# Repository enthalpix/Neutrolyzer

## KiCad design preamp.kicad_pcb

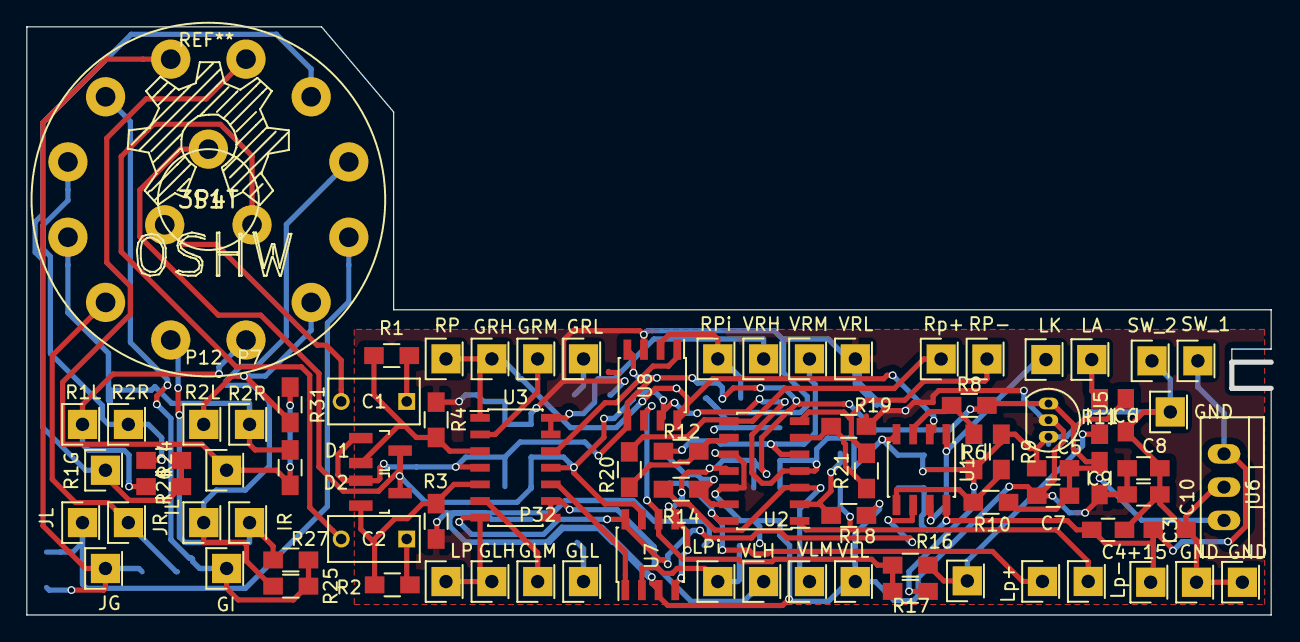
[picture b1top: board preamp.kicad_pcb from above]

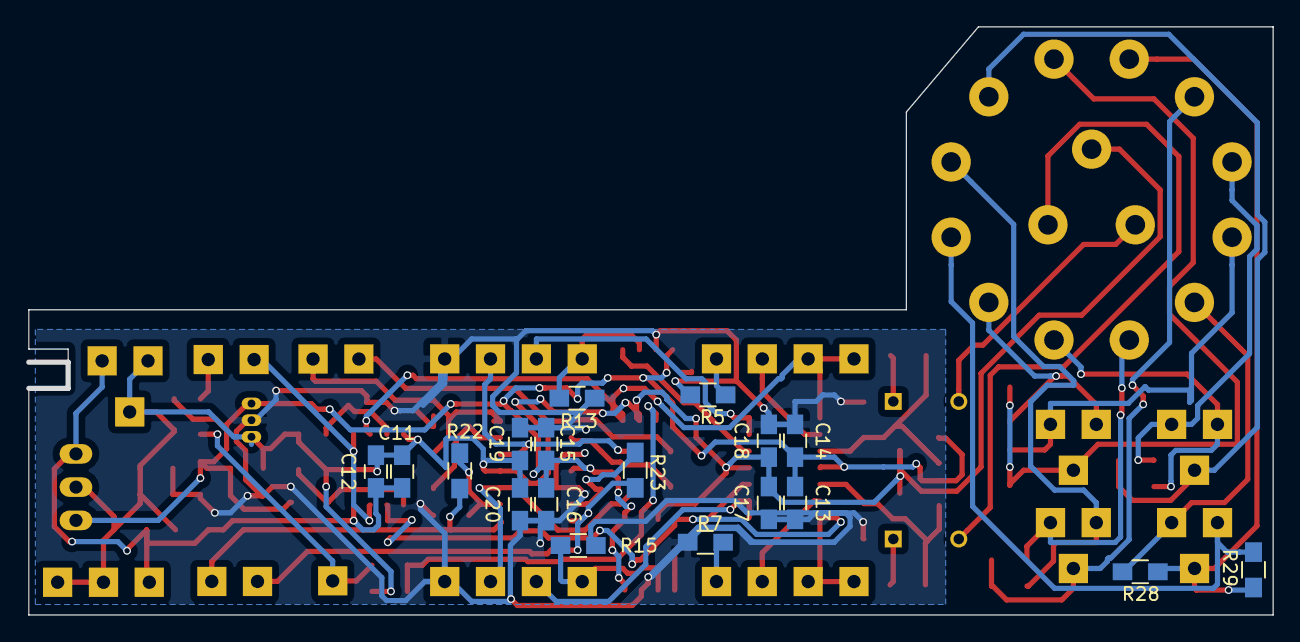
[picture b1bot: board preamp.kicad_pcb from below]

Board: 2 copper layers, 95.0 x 44.9 mm, 102 parts (18 on the bottom side), 50 nets.

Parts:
C1, C2: 470n; C_Rect_L7_W3.5_P5
C3, C5, C7, C8: 1µ; C_0805_HandSoldering
C4, C6, C9, C10, C12, C14, C16, C18, C20: 10n; C_0805_HandSoldering
C11, C13, C15, C17, C19: 100n; C_0805_HandSoldering
D1, D2: D_Schottky_x2_Serial; SOT-23_Handsoldering
P1: R1G; Socket_Strip_Straight_1x01
P2: IR; Socket_Strip_Straight_1x01
P3: GI; Socket_Strip_Straight_1x01
P4, P7: R2R; Socket_Strip_Straight_1x01
P5: IL; Socket_Strip_Straight_1x01
P6: R2G; Socket_Strip_Straight_1x01
P8: R1L; Socket_Strip_Straight_1x01
P9: JG; Socket_Strip_Straight_1x01
P10: JL; Socket_Strip_Straight_1x01
P11: JR; Socket_Strip_Straight_1x01
P12: R2L; Socket_Strip_Straight_1x01
P13, P14, P17: GND; Socket_Strip_Straight_1x01
P16: +15; Socket_Strip_Straight_1x01
P18: Lp-; Socket_Strip_Straight_1x01
P19: Rp+; Socket_Strip_Straight_1x01
P20: LP; Socket_Strip_Straight_1x01
P21: RP; Socket_Strip_Straight_1x01
P22: LPi; Socket_Strip_Straight_1x01
P23: RPi; Socket_Strip_Straight_1x01
P27: RP-; Socket_Strip_Straight_1x01
P28: Lp+; Socket_Strip_Straight_1x01
P29: GRM; Socket_Strip_Straight_1x01
P30: GRL; Socket_Strip_Straight_1x01
P31: GRH; Socket_Strip_Straight_1x01
P32: GLM; Socket_Strip_Straight_1x01
P33: GLL; Socket_Strip_Straight_1x01
P34: GLH; Socket_Strip_Straight_1x01
P35: LK; Socket_Strip_Straight_1x01
P36: SW_1; Socket_Strip_Straight_1x01
P37: SW_com; Socket_Strip_Straight_1x01
P38: SW_2; Socket_Strip_Straight_1x01
P39: LA; Socket_Strip_Straight_1x01
P40: VRH; Socket_Strip_Straight_1x01
P41: VLL; Socket_Strip_Straight_1x01
P42: VLH; Socket_Strip_Straight_1x01
P43: VRM; Socket_Strip_Straight_1x01
P44: VRL; Socket_Strip_Straight_1x01
P45: VLM; Socket_Strip_Straight_1x01
R1, R2, R12, R14, R18, R19, R20, R21, R22, R23: 10k; R_0805_HandSoldering
R3, R4, R24, R25, R26, R27, R28, R29, R30, R31: 1M; R_0805_HandSoldering
R5, R7: 2.2k; R_0805_HandSoldering
R6, R8, R9, R10: TBD; R_0805_HandSoldering
R11: 4.7k; R_0805_HandSoldering
R13, R15: 1.8k; R_0805_HandSoldering
R16: 50k; R_0805_HandSoldering
R17: 100k; R_0805_HandSoldering
S1: 3P4T; A
U1: LM193; SOIC-8_3.9x4.9mm_Pitch1.27mm
U2, U3: TL074; SOIC-14_3.9x8.7mm_Pitch1.27mm
U5: TLE2426; TO-92_Inline_Narrow_Oval
U6: LM7812; LDO_TO220
U7, U8: DG419; SOIC-8_3.9x4.9mm_Pitch1.27mm

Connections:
+6VA: C5.2, C6.2, C7.1, C9.1, C13.1, C14.1, C15.1, C16.1, D1.1, D2.1, R8.1, R10.2, U2.11, U3.4, U5.1, U6.VO, U7.4, U7.5, U8.4, U8.5
+15V: C3.1, C4.1, C11.1, C12.1, P16.1, P36.1, U1.8, U6.VI
/GI: P3.1, R25.1, R27.2, S1.5
/GJ: P9.1, R28.1, R29.1, S1.6
/GRCA: P1.1, R24.1, R26.2, S1.8
/GRCA2: P6.1, R30.1, R31.1, S1.7
/L_pow+: P28.1, R23.1, U2.14
/L_pow-: P18.1, R22.1, U2.1
/R_pow+: P19.1, R20.1, U2.8
/R_pow-: P27.1, R21.1, U2.7
GND: C3.2, C4.2, C5.1, C6.1, C8.2, C10.2, C11.2, C12.2, C17.2, C18.2, C19.2, C20.2, D1.3, D2.3, P13.1, P14.1, P17.1, P38.1, R6.2, R9.2, R17.1, S1.B, U1.4, U2.4, U3.11, U5.3, U6.GND, U7.7, U8.7
GNDA: C7.2, C8.1, C9.2, C10.1, C13.2, C14.2, C15.2, C16.2, C17.1, C18.1, C19.1, C20.1, P41.1, P44.1, R3.1, R4.1, R5.1, R7.1, R13.1, R15.1, R18.1, R19.1, U2.10, U2.12, U5.2, U7.3, U8.3
unnamed: C1.1, R1.2
unnamed: C1.2, S1.A
unnamed: C2.1, R2.2
unnamed: C2.2, S1.C
unnamed: D1.2, R1.1, R4.2, U3.3
unnamed: D2.2, R2.1, R3.2, U3.5
unnamed: P2.1, R27.1, S1.1
unnamed: P4.1, R24.2, S1.4
unnamed: P5.1, R25.2, S1.9
unnamed: P7.1, R30.2, S1.3
unnamed: P8.1, R26.1, S1.12
unnamed: P10.1, R29.2, S1.10
unnamed: P11.1, R28.2, S1.2
unnamed: P12.1, R31.2, S1.11
unnamed: P20.1, P34.1, U1.6, U3.7, U7.8
unnamed: P21.1, P31.1, U1.2, U3.1, U8.8
unnamed: P22.1, R15.2, U7.2
unnamed: P23.1, R13.2, U8.2
unnamed: P29.1, U3.2
unnamed: P30.1, R5.2
unnamed: P32.1, U3.6
unnamed: P33.1, R7.2
unnamed: P35.1, U1.1, U1.7
unnamed: P37.1, R11.2, R16.1
unnamed: P39.1, R11.1
unnamed: P40.1, U3.13, U3.14
unnamed: P42.1, U3.8, U3.9
unnamed: P43.1, R12.2, U2.5
unnamed: P45.1, R14.2, U2.3
unnamed: R6.1, R8.2, U1.3
unnamed: R9.1, R10.1, U1.5
unnamed: R12.1, R20.2, U2.9
unnamed: R14.1, R23.2, U2.13
unnamed: R16.2, R17.2, U7.6, U8.6
unnamed: R18.2, R22.2, U2.2
unnamed: R19.2, R21.2, U2.6
unnamed: U3.10, U7.1
unnamed: U3.12, U8.1

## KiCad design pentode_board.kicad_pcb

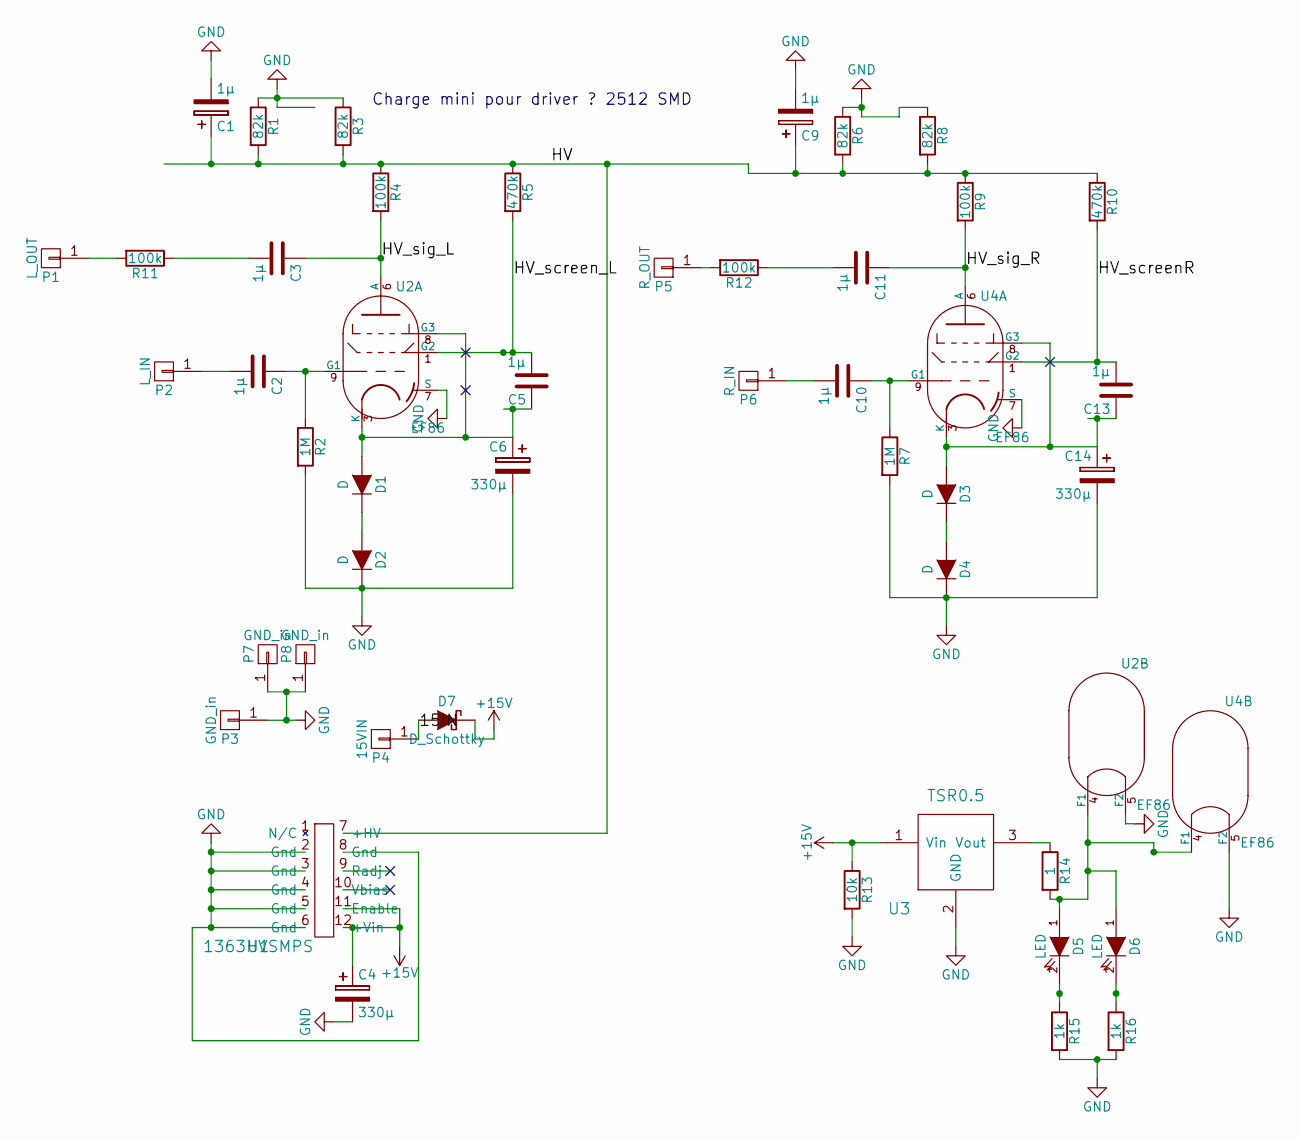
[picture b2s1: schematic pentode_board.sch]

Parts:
C1, C5, C9, C13: 1µ; C_Radial_D6.3_L11.2_P2.5
C2, C10: 1µ; C_Rect_L7_W3.5_P5
C3, C11: 1µ; C_Rect_L27_W11_P22
C4: 330µ; C_Radial_D12.5_L25_P5
C6, C14: 330µ; c_elec_6.3x7.7
D1, D2, D3, D4: D; D_0805_HandSoldering
D5, D6: LED; LED-3MM
D7: D_Schottky
P1: L_OUT; Pin_Header_Straight_1x01
P2: L_IN; Pin_Header_Straight_1x01
P3, P7, P8: GND_in; Pin_Header_Straight_1x01
P4: 15VIN; Pin_Header_Straight_1x01
P5: R_OUT; Pin_Header_Straight_1x01
P6: R_IN; Pin_Header_Straight_1x01
R1, R3, R6, R8: 82k; R_2512_HandSoldering
R2, R7: 1M; R_0805_HandSoldering
R4, R9, R11, R12: 100k; R_1206_HandSoldering
R5, R10: 470k; R_1206_HandSoldering
R13: 10k; R_0805_HandSoldering
R14: 1; R_2512_HandSoldering
R15, R16: 1k; R_0805_HandSoldering
U1: 1363HVSMPS; PSU1363
U2, U4: EF86; VALVE-NOVAL_P
U3: TSR0.5

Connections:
+15V: C4.1, D7.1 (K), R13.1, U1.11 (Enable), U1.12 (+Vin), U3.1 (Vin)
/15IN: D7.2 (A), P4.1
/HV: C1.1, C9.1, R1.2, R3.2, R4.1, R5.1, R6.2, R8.2, R9.1, R10.1, U1.7 (+HV)
/HV_screenR: C13.2, R10.2, U4.1 (G2)
/HV_screen_L: C5.2, R5.2, U2.1 (G2)
/HV_sig_L: C3.1, R4.2, U2.6 (A)
/HV_sig_R: C11.1, R9.2, U4.6 (A)
GND: C1.2, C4.2, C6.2, C9.2, C14.2, D2.2 (K), D4.2 (K), P3.1, P7.1, P8.1, R1.1, R2.2, R3.1, R6.1, R7.2, R8.1, R13.2, R15.2, R16.2, U1.2 (Gnd), U1.3 (Gnd), U1.4 (Gnd), U1.5 (Gnd), U1.6 (Gnd), U1.8 (Gnd), U2.5 (F2), U2.7 (S), U3.2 (GND), U4.5 (F2), U4.7 (S)
unnamed: C2.1, R2.1, U2.9 (G1)
unnamed: C2.2, P2.1
unnamed: C3.2, R11.1
unnamed: C5.1, C6.1, D1.1 (A), U2.3 (K), U2.8 (G3)
unnamed: C10.1, R7.1, U4.9 (G1)
unnamed: C10.2, P6.1
unnamed: C11.2, R12.1
unnamed: C13.1, C14.1, D3.1 (A), U4.3 (K), U4.8 (G3)
unnamed: D1.2 (K), D2.1 (A)
unnamed: D3.2 (K), D4.1 (A)
unnamed: D5.1 (A), D6.1 (A), R14.2, U2.4 (F1), U4.4 (F1)
unnamed: D5.2 (K), R15.1
unnamed: D6.2 (K), R16.1
unnamed: P1.1, R11.2
unnamed: P5.1, R12.2
unnamed: R14.1, U3.3 (Vout)

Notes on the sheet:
Charge mini pour driver ? 2512 SMD

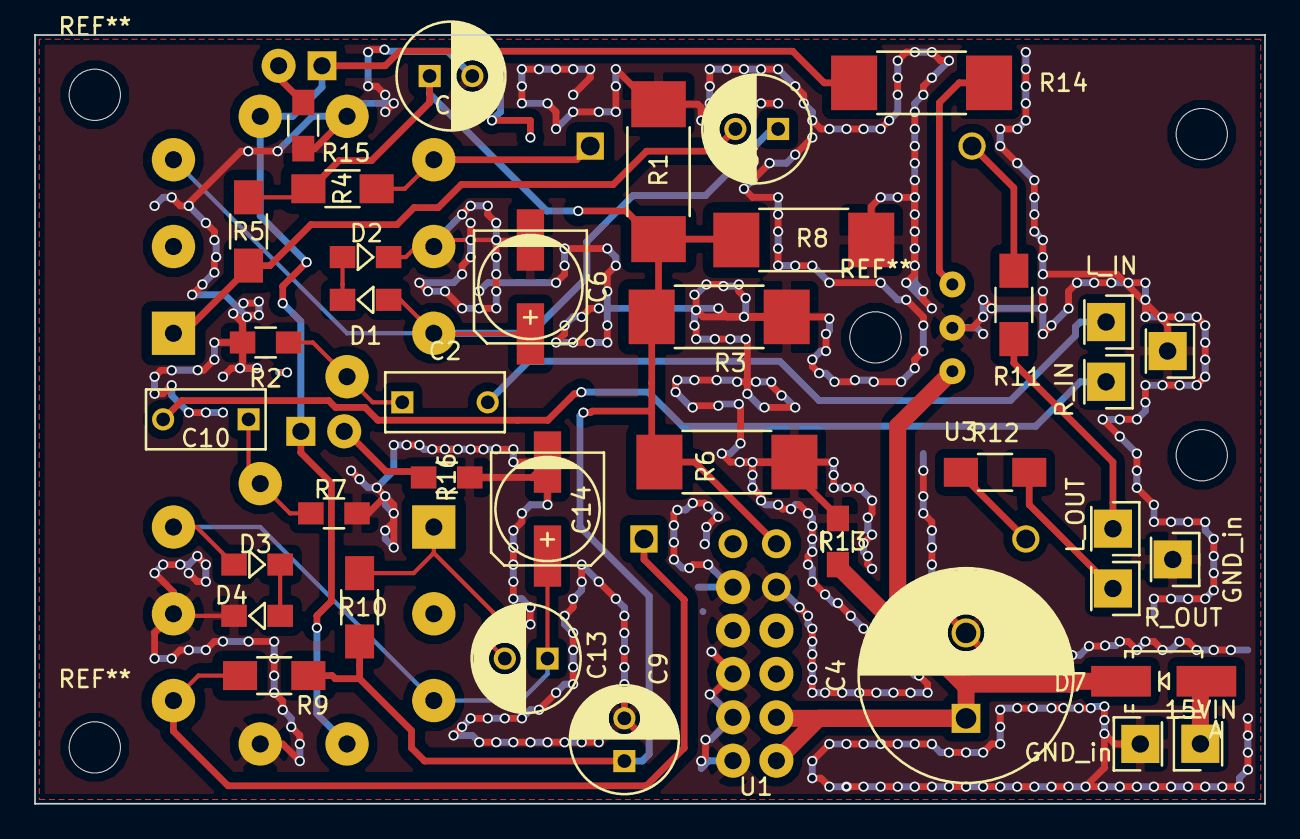
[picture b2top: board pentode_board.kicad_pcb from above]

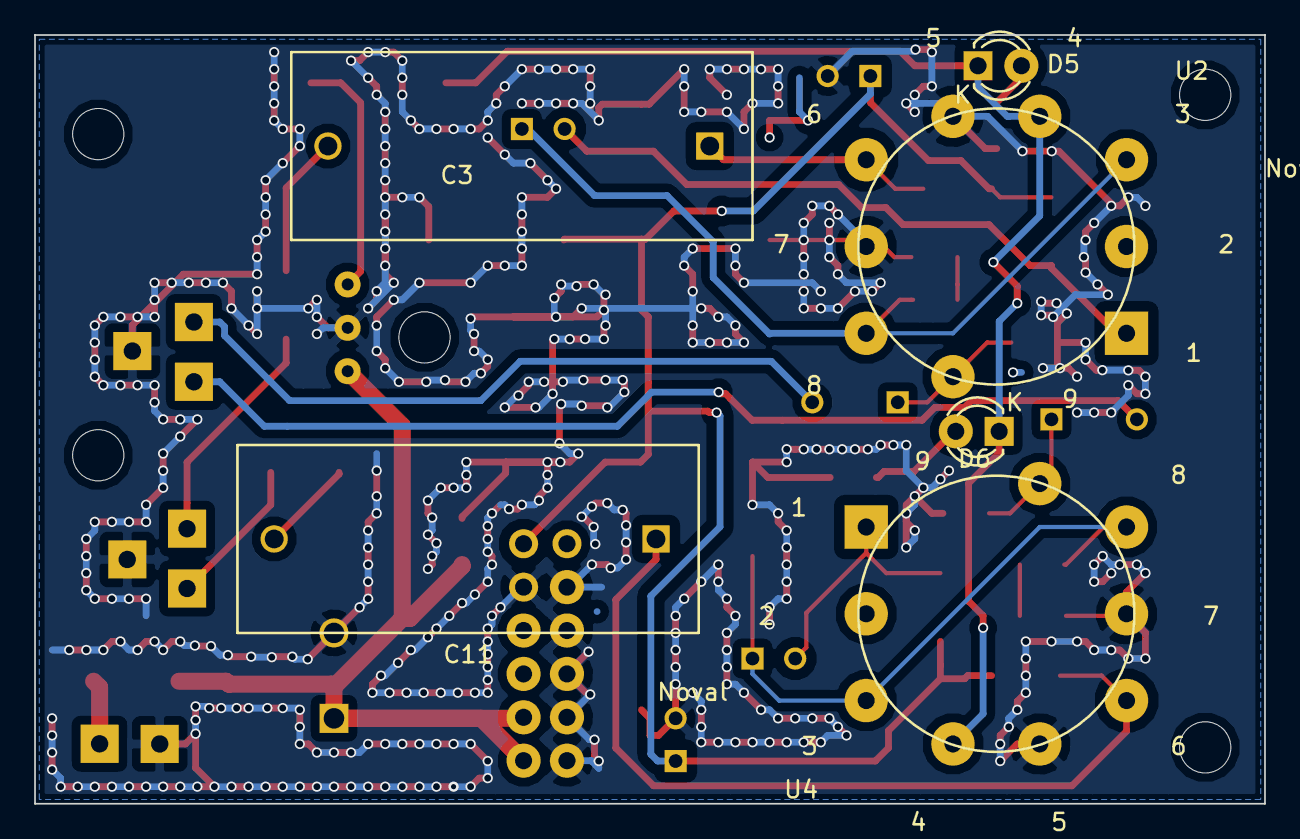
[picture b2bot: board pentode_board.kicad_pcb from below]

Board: 2 copper layers, 72.0 x 45.0 mm, 46 parts (6 on the bottom side), 24 nets.

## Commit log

2015-05-07 :neckbeard: Added .gitattributes & .gitignore files
2015-05-07 Creation
2015-05-07 Silkscreen fix
2015-05-07 1M to gnd on all inputs
    Added 1M to ground to avoid floating inputs
2015-05-07 Gerber generation
2015-05-07 Regenerated schematics pdf
2015-05-08 Updated BOM
2015-05-08 After today's review: - Adjusted a few things on PCB layout - Updated and renamed BOM - Removed some junk files
2015-05-08 Woops, updated BOM had somehow got lost
2015-05-16 Updated BoM... (as was ordered)
